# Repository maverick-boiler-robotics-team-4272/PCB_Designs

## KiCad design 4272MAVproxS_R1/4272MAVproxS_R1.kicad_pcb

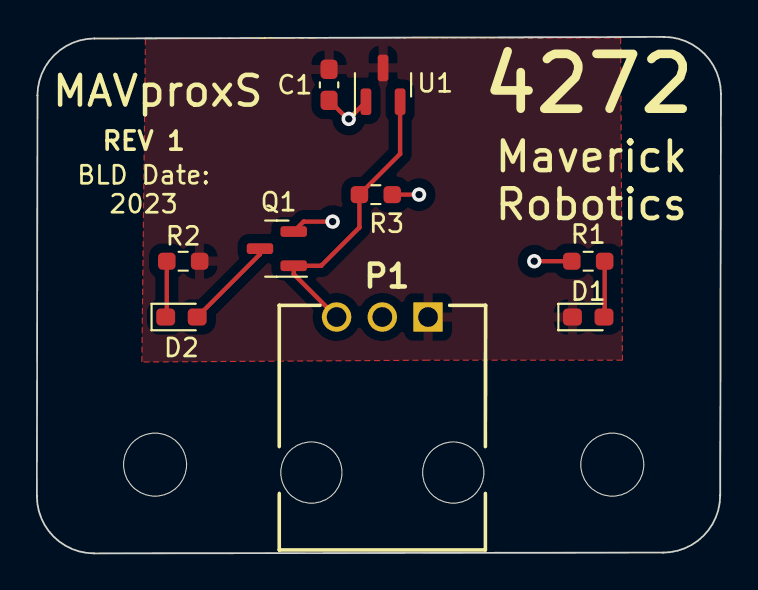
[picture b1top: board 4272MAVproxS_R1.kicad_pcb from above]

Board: 2 copper layers, 38.0 x 28.7 mm, 9 parts (0 on the bottom side), 6 nets.

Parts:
C1: 100nF; C_0603_1608Metric_Pad1.08x0.95mm_HandSolder
D1: RED; LED_0603_1608Metric_Pad1.05x0.95mm_HandSolder
D2: GRN; LED_0603_1608Metric_Pad1.05x0.95mm_HandSolder
P1: 15-91-7030; 705550037
Q1: FDN338P; SOT-23
R1, R2: 137; R_0603_1608Metric_Pad0.98x0.95mm_HandSolder
R3: 100K; R_0603_1608Metric_Pad0.98x0.95mm_HandSolder
U1: DRV5032FCBZR; SOT-23

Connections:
+3.3V: C1.1, P1.2, Q1.2 (S), R1.1, R3.2, U1.1 (VCC)
GND: C1.2, D1.1 (K), P1.1, R2.2, U1.3 (GND)
unnamed: D1.2 (A), R1.2
unnamed: D2.2 (A), Q1.3 (D)
unnamed: D2.1 (K), R2.1
unnamed: P1.3, Q1.1 (G), R3.1, U1.2 (OUT)

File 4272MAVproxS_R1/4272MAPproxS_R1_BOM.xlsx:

Line # | Ref Des | Quantity | Decription | Manufacturer | Part # | Footprint
1 | C1 | 1 | CAP CER 10000PF 50V C0G/NP0 | Murata | GRM1885C1H103JA01J | 0603
2 | D1 | 1 | LED T-1 Through hole red | Lite-On | LTL-4211N | T1
3 | D2 | 1 | LED T-1 Through hole green | Lite-On | LTL-45231 | T1
4 | P1 | 1 | SL Conn Header R/A 3Pos 2.54MM | Molex | 705550037 | SL RA 3
5 | Q1 | 1 | MOSFET P-CH 20V 1.6A | onsemi | FDN338P | SOT-23
6 | R1,R2 | 2 | RES 137 OHM 1% 1/10W | YAGEO | RC0603FR-07137RL | 0603
7 | R3 | 1 | RES 100k OHM 1% 1/10W | YAGEO | RC0603FR-07100KL | 0603
8 | U1 | 1 | Hall Effect Sensor Omnipolar | Texas Instruments | DRV5032FCLPGM | TO-92

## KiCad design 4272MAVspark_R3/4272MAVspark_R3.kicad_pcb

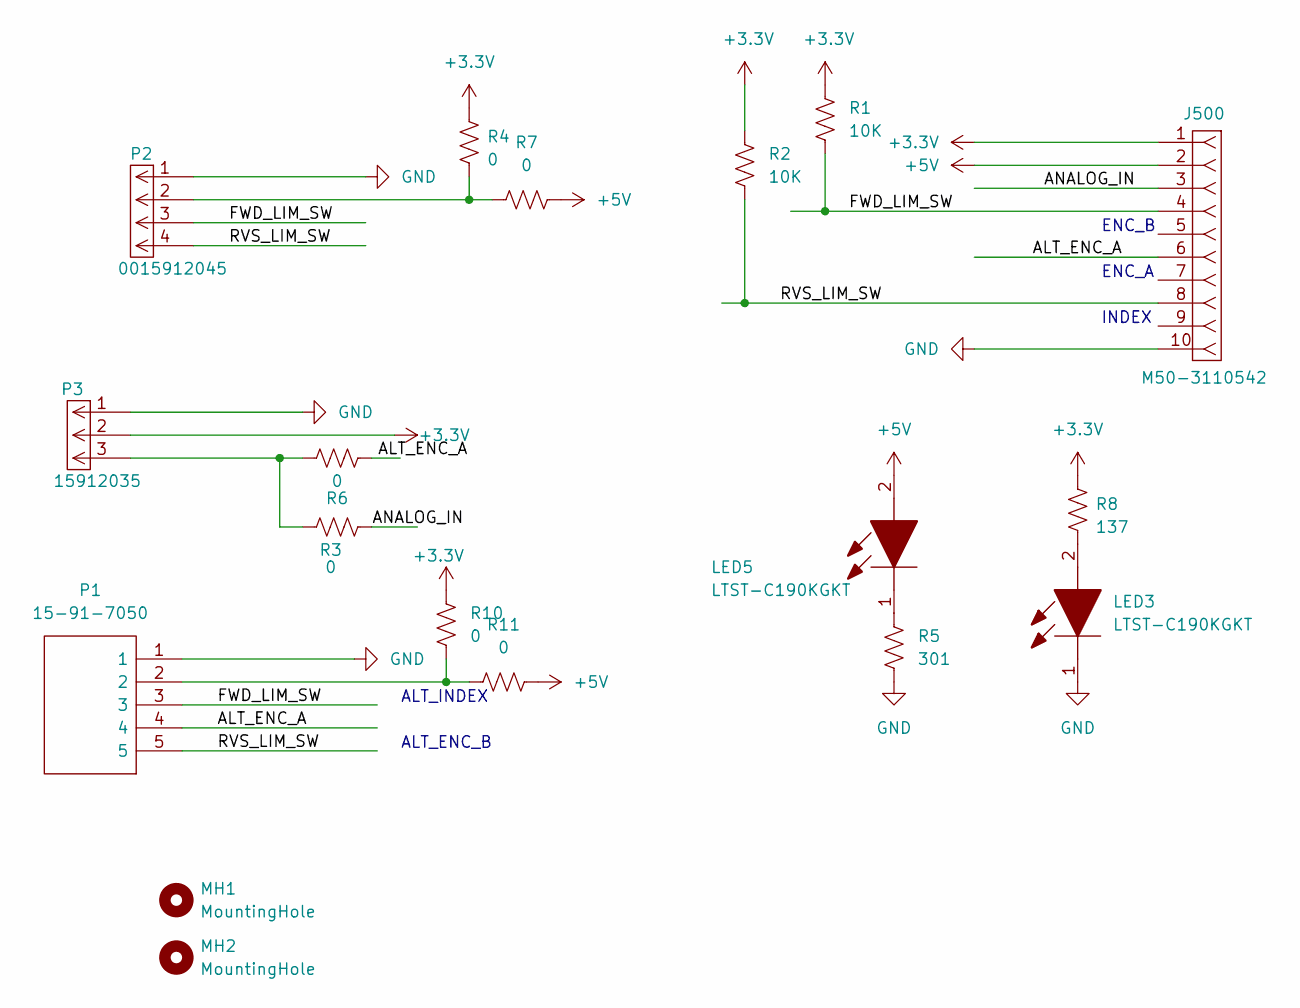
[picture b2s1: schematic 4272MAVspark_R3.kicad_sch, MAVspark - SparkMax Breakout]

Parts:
J500: M50-3110542; M503110542; Mouser Part Number 855-M50-3110542
LED3, LED5: LTST-C190KGKT; LED_0603_1608Metric_Pad1.05x0.95mm_HandSolder; Mouser Part Number 859-LTST-C190KGKT
MH1, MH2: MountingHole; MountingHole_3.2mm_M3
P1: 15-91-7050; 15917050; Manufacturer_Part_Number 15-91-7050; Mouser Part Number 538-15-91-7050
P2: 0015912045; Manufacturer_Part_Number 0015912045; Mouser Part Number N/A
P3: 15912035; Mouser Part Number 538-15-91-7030
R1, R2: 10K; R_0603_1608Metric_Pad0.98x0.95mm_HandSolder
R3, R4, R6, R7, R10, R11: 0; R_0805_2012Metric_Pad1.20x1.40mm_HandSolder
R5: 301; R_0603_1608Metric_Pad0.98x0.95mm_HandSolder
R8: 137; R_0603_1608Metric_Pad0.98x0.95mm_HandSolder

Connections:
+3.3V: J500.1, P3.2, R1.2, R2.1, R4.2, R8.1, R10.1
+5V: J500.2, LED5.2, R7.1, R11.1
/ALT_ENC_A: J500.6, P1.4, R6.2
/ANALOG_IN: J500.3, R3.2
/FWD_LIM_SW: J500.4, P1.3, P2.3, R1.1
/RVS_LIM_SW: J500.8, P1.5, P2.4, R2.2
GND: J500.10, LED3.1, P1.1, P2.1, P3.1, R5.2
unnamed: LED3.2, R8.2
unnamed: LED5.1, R5.1
unnamed: P1.2, R10.2, R11.2
unnamed: P2.2, R4.1, R7.2
unnamed: P3.3, R3.1, R6.1

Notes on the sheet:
ALT_ENC_B
ALT_INDEX
ENC_B
INDEX
ENC_A

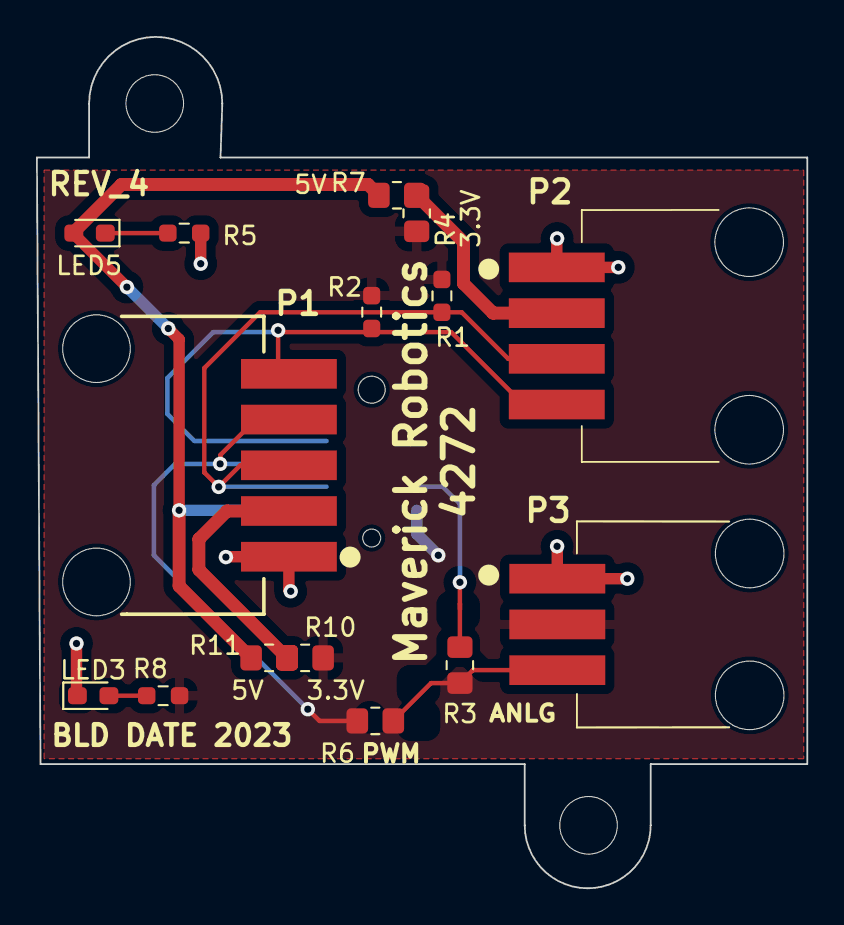
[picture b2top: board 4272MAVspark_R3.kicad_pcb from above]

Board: 2 copper layers, 42.8 x 47.3 mm, 17 parts (1 on the bottom side), 12 nets.

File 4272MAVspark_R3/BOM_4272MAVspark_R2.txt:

REFDES	QTY	DIGI-KEY #		MANUF		PART #			DESCRIPTION
LED3	1	160-1435-1-ND		Lite-On Inc.	LTST-C190KGKT		LED GREEN 0603 SMD
LED5	1	160-1435-1-ND		Lite-On Inc.	LTST-C190KGKT		LED GREEN 0603 SMD
R1, R2	2									RES 10K
R3	1	311-137HRCT-ND		YAGEO		RC0603FR-07137RL	RES 137 0603 1%	
R5	1									RES 301 0603 1%
R6	0									RES 0 0805
R7	1									RES 0 0805
R10	0									RES 0 0805
R11	0									RES 0 0805
P1	0
P2	1
P3	1
J500	1

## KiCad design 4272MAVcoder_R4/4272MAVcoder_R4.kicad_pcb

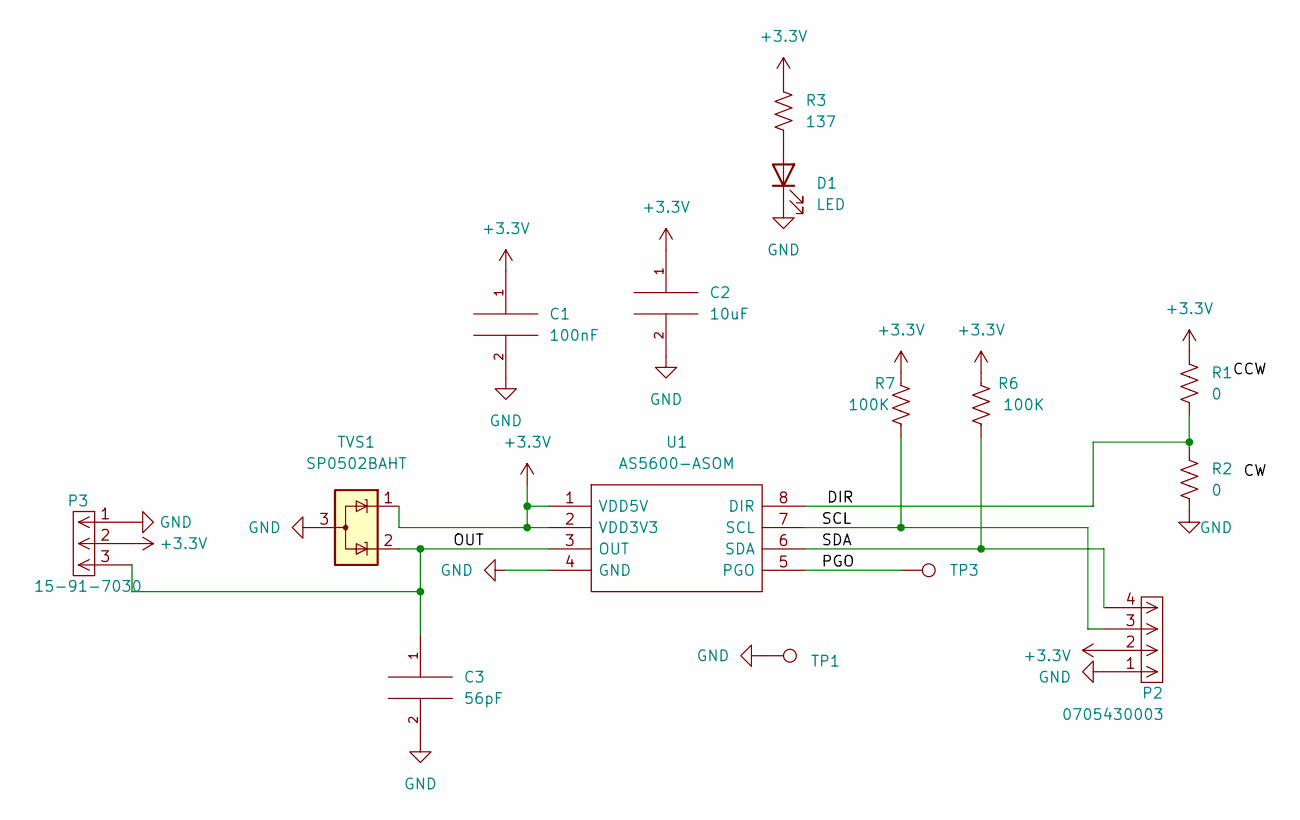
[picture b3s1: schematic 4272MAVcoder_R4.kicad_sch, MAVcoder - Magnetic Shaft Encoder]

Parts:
C1: 100nF; C_0603_1608Metric_Pad1.08x0.95mm_HandSolder
C2: 10uF; C_0805_2012Metric_Pad1.18x1.45mm_HandSolder
C3: 56pF; C_0603_1608Metric_Pad1.08x0.95mm_HandSolder
D1: LED; LED_D3.0mm
P2: 0705430003; Molex_SL_171971-0004_1x04_P2.54mm_Vertical; Manufacturer_Part_Number 0015912045; Mouser Part Number N/A
P3: 15-91-7030; 705550037; Mouser Part Number 538-15-91-7030
R1, R2: 0; R_0603_1608Metric_Pad0.98x0.95mm_HandSolder
R3: 137; R_0603_1608Metric_Pad0.98x0.95mm_HandSolder
R6, R7: 100K; R_0603_1608Metric_Pad0.98x0.95mm_HandSolder
TP1, TP3: TestPoint; TestPoint_THTPad_1.0x1.0mm_Drill0.5mm
TVS1: SP0502BAHT; SOT-23
U1: AS5600-ASOM; SOIC-8_3.9x4.9mm_P1.27mm; Mouser Part Number 985-AS5600-ASOM

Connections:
+3.3V: C1.1, C2.1, P2.2, R1.1, R3.1, R6.2, R7.2, TVS1.1 (K), U1.1 (VDD5V), U1.2 (VDD3V3); also elsewhere on the board
/DIR: R1.2, R2.1, U1.8 (DIR)
/OUT: C3.1, TVS1.2 (K), U1.3 (OUT); also elsewhere on the board
/PGO: TP3.1, U1.5 (PGO)
/SCL: P2.3, R7.1, U1.7 (SCL)
/SDA: P2.4, R6.1, U1.6 (SDA)
GND: C1.2, C2.2, C3.2, D1.1 (K), P2.1, R2.2, TP1.1, TVS1.3 (A), U1.4 (GND); also elsewhere on the board
unnamed: D1.2 (A), R3.2

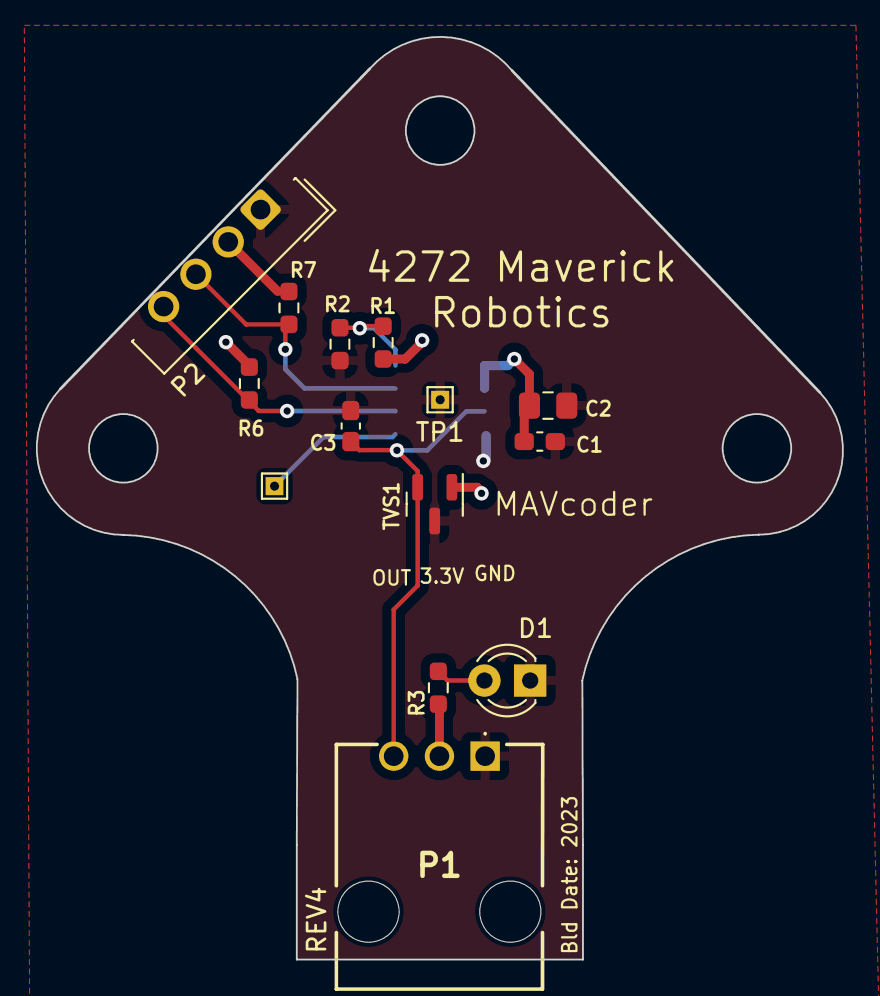
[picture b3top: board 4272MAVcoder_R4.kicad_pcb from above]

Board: 2 copper layers, 44.8 x 51.3 mm, 15 parts (1 on the bottom side), 8 nets.

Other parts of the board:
P1: 15-91-7030; 705550037

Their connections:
+3.3V: P1.2; also elsewhere on the board
/OUT: P1.3; also elsewhere on the board
GND: P1.1; also elsewhere on the board

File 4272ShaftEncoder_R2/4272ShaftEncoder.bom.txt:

REFDES	QTY	DIGI-KEY #		MANUF		PART #			DESCRIPTION
C1	1	587-1245-1-ND 		Taiyo Yuden	TMK107BJ104KA-T		CAP 0.1uF 0603 10% SMD
C2	1	587-1300-1-ND		Taiyo Yuden	LMK212BJ106KG-T		CAP 10uF 0805 10% SMD
C3	1	311-1066-1-ND		YAGEO		CC0603JRNPO9BN560	CAP 56pF 0603 SMD
LED3	1	160-1435-1-ND		Lite-On Inc.	LTST-C190KGKT		LED GREEN 0603 SMD
R1	1	311-0.0HRCT-ND		YAGEO		RC0603FR-070RL		RES 0 0603
R3	1	311-137HRCT-ND		YAGEO		RC0603FR-07137RL	RES 137 0603 1%	
R6,R7	2	311-100KLDCT-ND		YAGEO		AC0603FR-07100KL	RES 100K 0603 1%
TVS1 	1	F2714CT-ND		Littelfuse Inc.	SP0502BAHTG		TVS 8.5V CLAMP	
U1	1	AS5600-ASOMCT-ND	ams		AS5600-ASOM		Hall Effect Angle Sensor

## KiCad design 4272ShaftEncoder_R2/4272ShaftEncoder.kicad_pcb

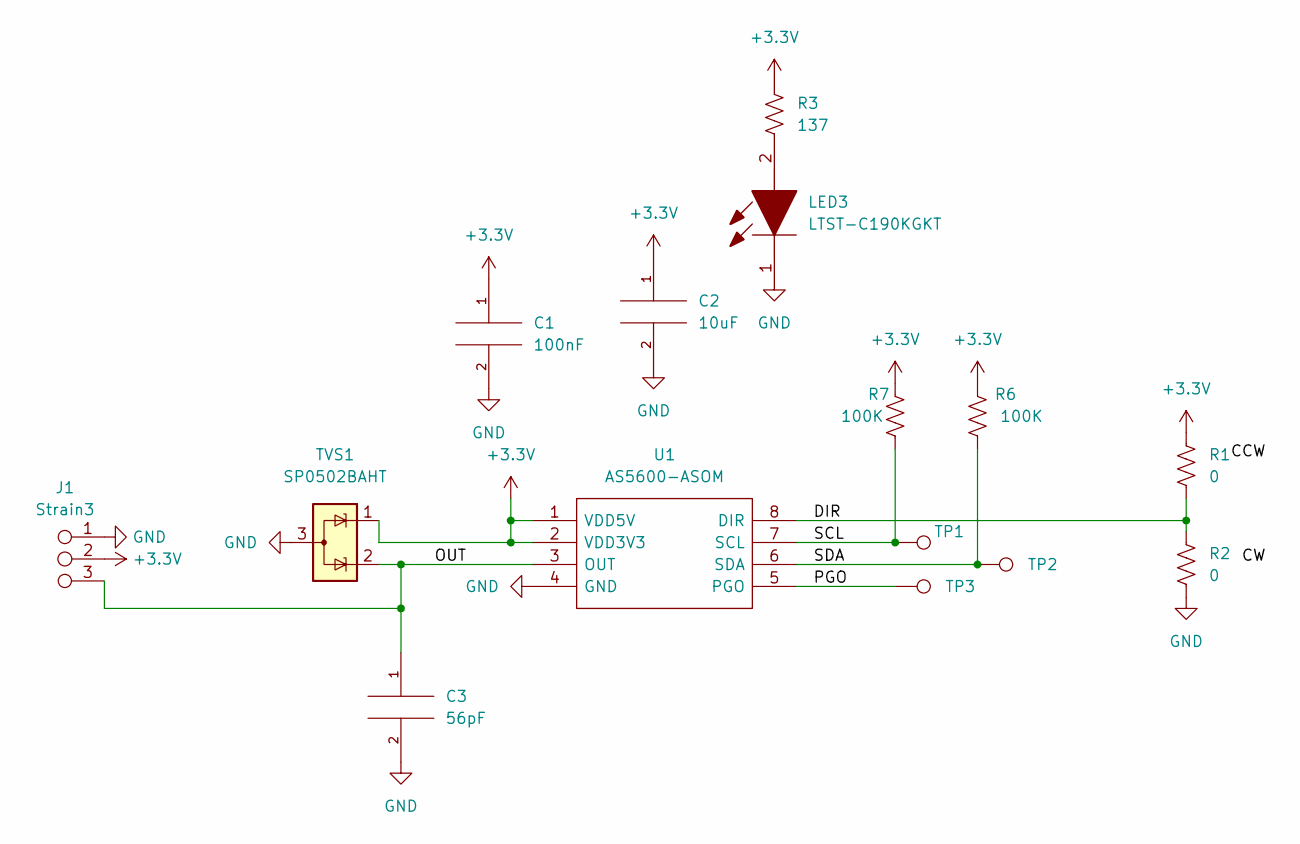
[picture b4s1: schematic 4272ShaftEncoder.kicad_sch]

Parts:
C1: 100nF; C_0603_1608Metric_Pad1.08x0.95mm_HandSolder
C2: 10uF; C_0805_2012Metric_Pad1.18x1.45mm_HandSolder
C3: 56pF; C_0603_1608Metric_Pad1.08x0.95mm_HandSolder
J1: Strain3; 3Pin Strain Relief 1x03 2.54mm
LED3: LTST-C190KGKT; LED_0603_1608Metric_Pad1.05x0.95mm_HandSolder; Mouser Part Number 859-LTST-C190KGKT
R1, R2: 0; R_0603_1608Metric_Pad0.98x0.95mm_HandSolder
R3: 137; R_0603_1608Metric_Pad0.98x0.95mm_HandSolder
R6, R7: 100K; R_0603_1608Metric_Pad0.98x0.95mm_HandSolder
TP1, TP2, TP3: TestPoint; TestPoint_THTPad_1.0x1.0mm_Drill0.5mm
TVS1: SP0502BAHT; SOT-23
U1: AS5600-ASOM; SOIC-8_3.9x4.9mm_P1.27mm; Mouser Part Number 985-AS5600-ASOM

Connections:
+3.3V: C1.1, C2.1, J1.2, R1.1, R3.1, R6.2, R7.2, TVS1.1 (K), U1.1 (VDD5V), U1.2 (VDD3V3)
/DIR: R1.2, R2.1, U1.8 (DIR)
/OUT: C3.1, J1.3, TVS1.2 (K), U1.3 (OUT)
/PGO: TP3.1, U1.5 (PGO)
/SCL: R7.1, TP1.1, U1.7 (SCL)
/SDA: R6.1, TP2.1, U1.6 (SDA)
GND: C1.2, C2.2, C3.2, J1.1, LED3.1, R2.2, TVS1.3 (A), U1.4 (GND)
unnamed: LED3.2, R3.2

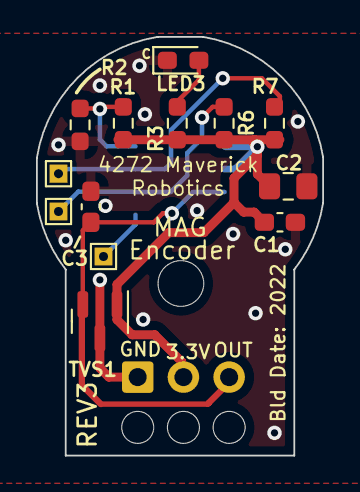
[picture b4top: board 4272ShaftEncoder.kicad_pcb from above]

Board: 2 copper layers, 15.9 x 23.3 mm, 15 parts (1 on the bottom side), 8 nets.

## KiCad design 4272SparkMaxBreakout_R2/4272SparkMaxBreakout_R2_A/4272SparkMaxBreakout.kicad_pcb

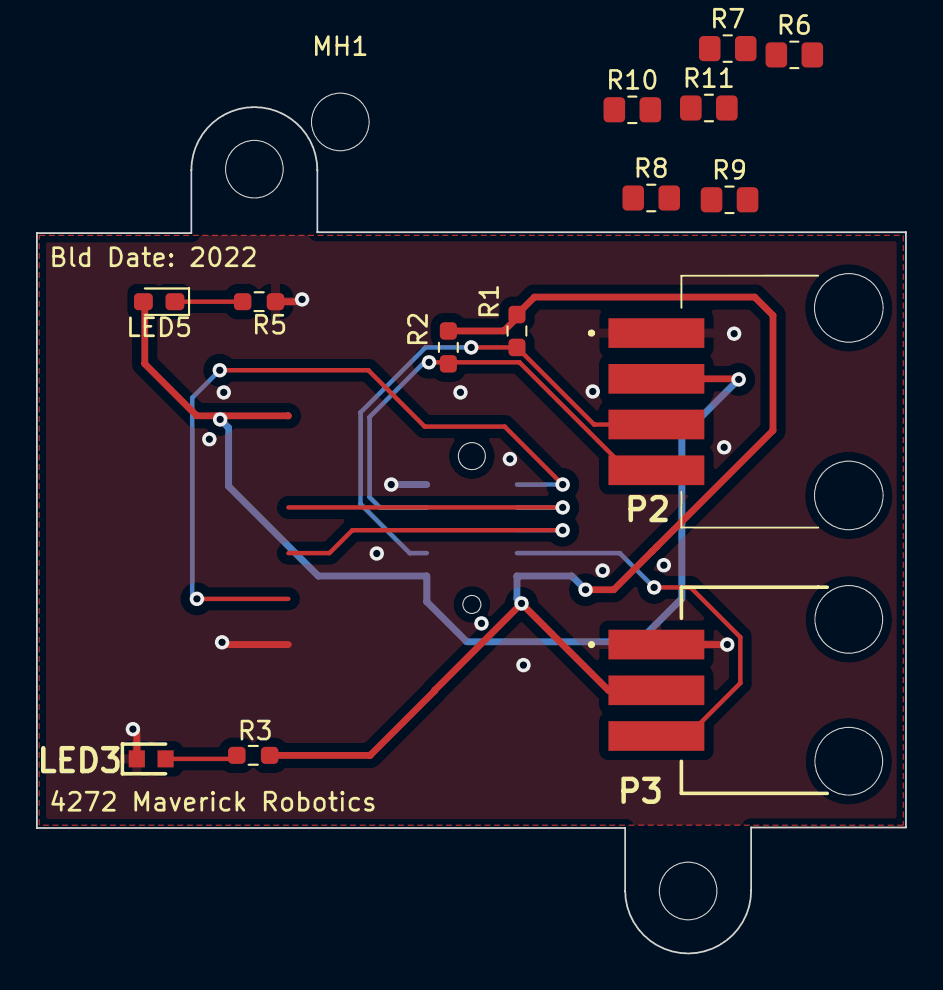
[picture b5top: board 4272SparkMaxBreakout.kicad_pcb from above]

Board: 2 copper layers, 48.3 x 47.0 mm, 17 parts (1 on the bottom side), 10 nets.

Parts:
J500: M50-3110542; M503110542_MOD
LED3: LTST-C190KGKT; LEDC1608X80N
LED5: LTST-C190KGKT; LED_0603_1608Metric_Pad1.05x0.95mm_HandSolder
MH1, MH2: MountingHole; MountingHole_3.2mm_M3
P2: 0015912045
P3: 15-91-7030; 15917030
R1, R2: 10K; R_0603_1608Metric_Pad0.98x0.95mm_HandSolder
R3: 137; R_0603_1608Metric_Pad0.98x0.95mm_HandSolder
R5: 301; R_0603_1608Metric_Pad0.98x0.95mm_HandSolder
R6, R7, R8, R9, R10, R11: 0; R_0805_2012Metric_Pad1.20x1.40mm_HandSolder

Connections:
+3.3V: J500.1, P3.2, R1.2, R2.1, R3.1, R6.2, R8.1, R10.1
+5V: J500.2, LED5.2, P2.2, R7.1, R9.1, R11.1
/ANALOG_IN: J500.3, P3.3
/FWD_LIM_SW: J500.4, P2.3, R1.1
/RVS_LIM_SW: J500.8, P2.4, R2.2
GND: J500.10, LED3.1, P2.1, P3.1, R5.2
unnamed: LED5.1, R5.1
unnamed: R10.2, R11.2
unnamed: R6.1, R7.2
unnamed: R8.2, R9.2

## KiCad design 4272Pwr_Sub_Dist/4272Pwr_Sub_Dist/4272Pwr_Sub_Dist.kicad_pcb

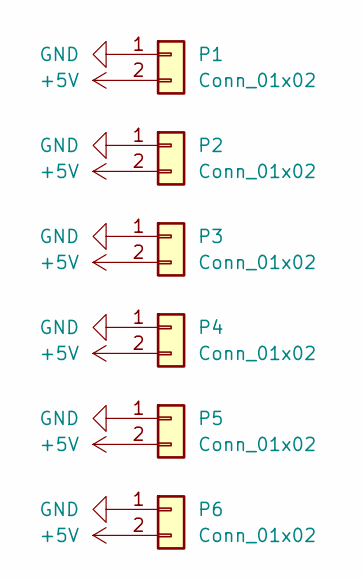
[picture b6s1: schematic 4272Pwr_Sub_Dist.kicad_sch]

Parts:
P1, P2, P3, P4, P5, P6: Conn_01x02; Molex_SL_171971-0002_1x02_P2.54mm_Vertical

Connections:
+5V: P1.2, P2.2, P3.2, P4.2, P5.2, P6.2
GND: P1.1, P2.1, P3.1, P4.1, P5.1, P6.1

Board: 2 copper layers, 6 parts (0 on the bottom side), 2 nets, no tracks yet.

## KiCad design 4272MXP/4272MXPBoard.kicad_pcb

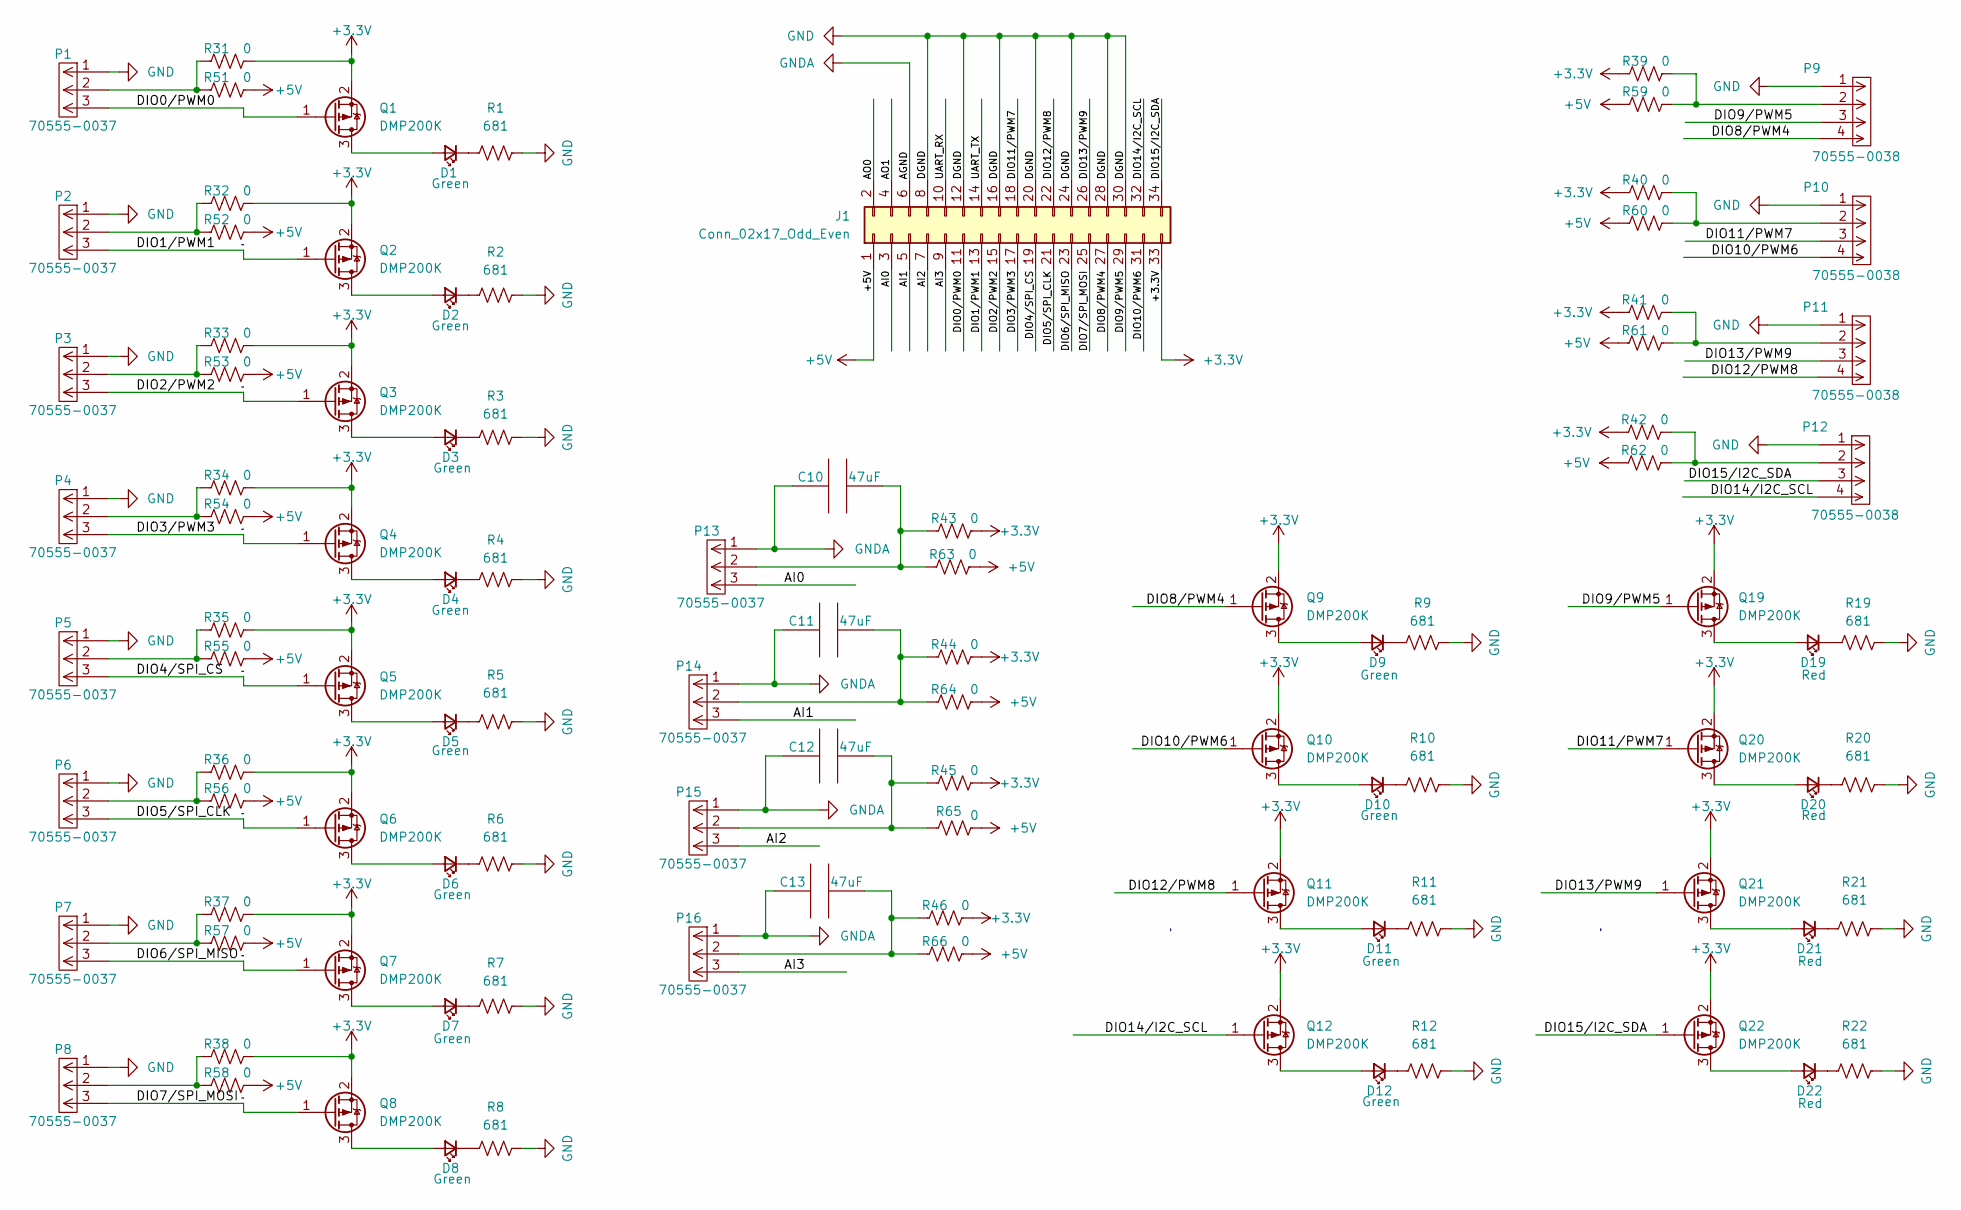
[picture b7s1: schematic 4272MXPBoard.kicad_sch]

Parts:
C10, C11, C12, C13: 47uF; C_0805_2012Metric_Pad1.18x1.45mm_HandSolder; Part # C2012X5R1A476M125AC
D1, D2, D3, D4, D5, D6, D7, D8, D9, D10, D11, D12: Green; LED_D3.0mm
D19, D20, D21, D22: Red; LED_D3.0mm
J1: Conn_02x17_Odd_Even; PinSocket_2x17_P2.54mm_Vertical
P1, P2, P3, P4, P5, P6, P7, P8, P13, P14, P15, P16: 70555-0037; 705550037; Mouser Part Number 538-15-91-7030
P9, P10, P11, P12: 70555-0038; 705550038; Mouser Part Number 538-15-91-7030
Q1, Q2, Q3, Q4, Q5, Q6, Q7, Q8, Q9, Q10, Q11, Q12, Q19, Q20, Q21, Q22: DMP200K; SOT-23
R1, R2, R3, R4, R5, R6, R7, R8, R9, R10, R11, R12, R19, R20, R21, R22: 681; R_0603_1608Metric_Pad0.98x0.95mm_HandSolder
R31, R32, R33, R34, R35, R36, R37, R38, R39, R40, R41, R42, R43, R44, R45, R46, R51, R52, R53, R54, R55, R56, R57, R58, R59, R60, R61, R62, R63, R64, R65, R66: 0; R_0805_2012Metric_Pad1.20x1.40mm_HandSolder

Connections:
+3.3V: J1.33, Q1.2 (S), Q2.2 (S), Q3.2 (S), Q4.2 (S), Q5.2 (S), Q6.2 (S), Q7.2 (S), Q8.2 (S), Q9.2 (S), Q10.2 (S), Q11.2 (S), Q12.2 (S), Q19.2 (S), Q20.2 (S), Q21.2 (S), Q22.2 (S), R31.2, R32.2, R33.2, R34.2, R35.2, R36.2, R37.2, R38.2, R39.1, R40.1, R41.1, R42.1, R43.2, R44.2, R45.2, R46.2
+5V: J1.1, R51.2, R52.2, R53.2, R54.2, R55.2, R56.2, R57.2, R58.2, R59.1, R60.1, R61.1, R62.1, R63.2, R64.2, R65.2, R66.2
/AI0: J1.3, P13.3
/AI1: J1.5, P14.3
/AI2: J1.7, P15.3
/AI3: J1.9, P16.3
/AO0: J1.2
/AO1: J1.4
/DIO0/PWM0: J1.11, P1.3, Q1.1 (G)
/DIO1/PWM1: J1.13, P2.3, Q2.1 (G)
/DIO2/PWM2: J1.15, P3.3, Q3.1 (G)
/DIO3/PWM3: J1.17, P4.3, Q4.1 (G)
/DIO4/SPI_CS: J1.19, P5.3, Q5.1 (G)
/DIO5/SPI_CLK: J1.21, P6.3, Q6.1 (G)
/DIO6/SPI_MISO: J1.23, P7.3, Q7.1 (G)
/DIO7/SPI_MOSI: J1.25, P8.3, Q8.1 (G)
/DIO8/PWM4: J1.27, P9.4, Q9.1 (G)
/DIO9/PWM5: J1.29, P9.3, Q19.1 (G)
/DIO10/PWM6: J1.31, P10.4, Q10.1 (G)
/DIO11/PWM7: J1.18, P10.3, Q20.1 (G)
/DIO12/PWM8: J1.22, P11.4, Q11.1 (G)
/DIO13/PWM9: J1.26, P11.3, Q21.1 (G)
/DIO14/I2C_SCL: J1.32, P12.4, Q12.1 (G)
/DIO15/I2C_SDA: J1.34, P12.3, Q22.1 (G)
/UART_RX: J1.10
/UART_TX: J1.14
GND: J1.8, J1.12, J1.16, J1.20, J1.24, J1.28, J1.30, P1.1, P2.1, P3.1, P4.1, P5.1, P6.1, P7.1, P8.1, P9.1, P10.1, P11.1, P12.1, R1.2, R2.2, R3.2, R4.2, R5.2, R6.2, R7.2, R8.2, R9.2, R10.2, R11.2, R12.2, R19.2, R20.2, R21.2, R22.2
GNDA: C10.1, C11.1, C12.1, C13.1, J1.6, P13.1, P14.1, P15.1, P16.1
unnamed: D1.1 (K), R1.1
unnamed: D1.2 (A), Q1.3 (D)
unnamed: D2.1 (K), R2.1
unnamed: D2.2 (A), Q2.3 (D)
unnamed: D3.1 (K), R3.1
unnamed: D3.2 (A), Q3.3 (D)
unnamed: D4.1 (K), R4.1
unnamed: D4.2 (A), Q4.3 (D)
unnamed: D5.1 (K), R5.1
unnamed: D5.2 (A), Q5.3 (D)
unnamed: D6.1 (K), R6.1
unnamed: D6.2 (A), Q6.3 (D)
unnamed: D7.1 (K), R7.1
unnamed: D7.2 (A), Q7.3 (D)
unnamed: D8.1 (K), R8.1
unnamed: D8.2 (A), Q8.3 (D)
unnamed: D9.1 (K), R9.1
unnamed: D9.2 (A), Q9.3 (D)
unnamed: D10.1 (K), R10.1
unnamed: D10.2 (A), Q10.3 (D)
unnamed: D11.1 (K), R11.1
unnamed: D11.2 (A), Q11.3 (D)
unnamed: D12.1 (K), R12.1
unnamed: D12.2 (A), Q12.3 (D)
unnamed: D19.1 (K), R19.1
unnamed: D19.2 (A), Q19.3 (D)
unnamed: D20.1 (K), R20.1
unnamed: D20.2 (A), Q20.3 (D)
unnamed: D21.1 (K), R21.1
unnamed: D21.2 (A), Q21.3 (D)
unnamed: D22.1 (K), R22.1
unnamed: D22.2 (A), Q22.3 (D)
unnamed: P1.2, R31.1, R51.1
unnamed: P2.2, R32.1, R52.1
unnamed: P3.2, R33.1, R53.1
unnamed: P4.2, R34.1, R54.1
unnamed: P5.2, R35.1, R55.1
unnamed: P6.2, R36.1, R56.1
unnamed: P7.2, R37.1, R57.1
unnamed: P8.2, R38.1, R58.1
unnamed: P9.2, R39.2, R59.2
unnamed: P10.2, R40.2, R60.2
unnamed: P11.2, R41.2, R61.2
unnamed: P12.2, R42.2, R62.2
unnamed: C10.2, P13.2, R43.1, R63.1
unnamed: C11.2, P14.2, R44.1, R64.1
unnamed: C12.2, P15.2, R45.1, R65.1
unnamed: C13.2, P16.2, R46.1, R66.1

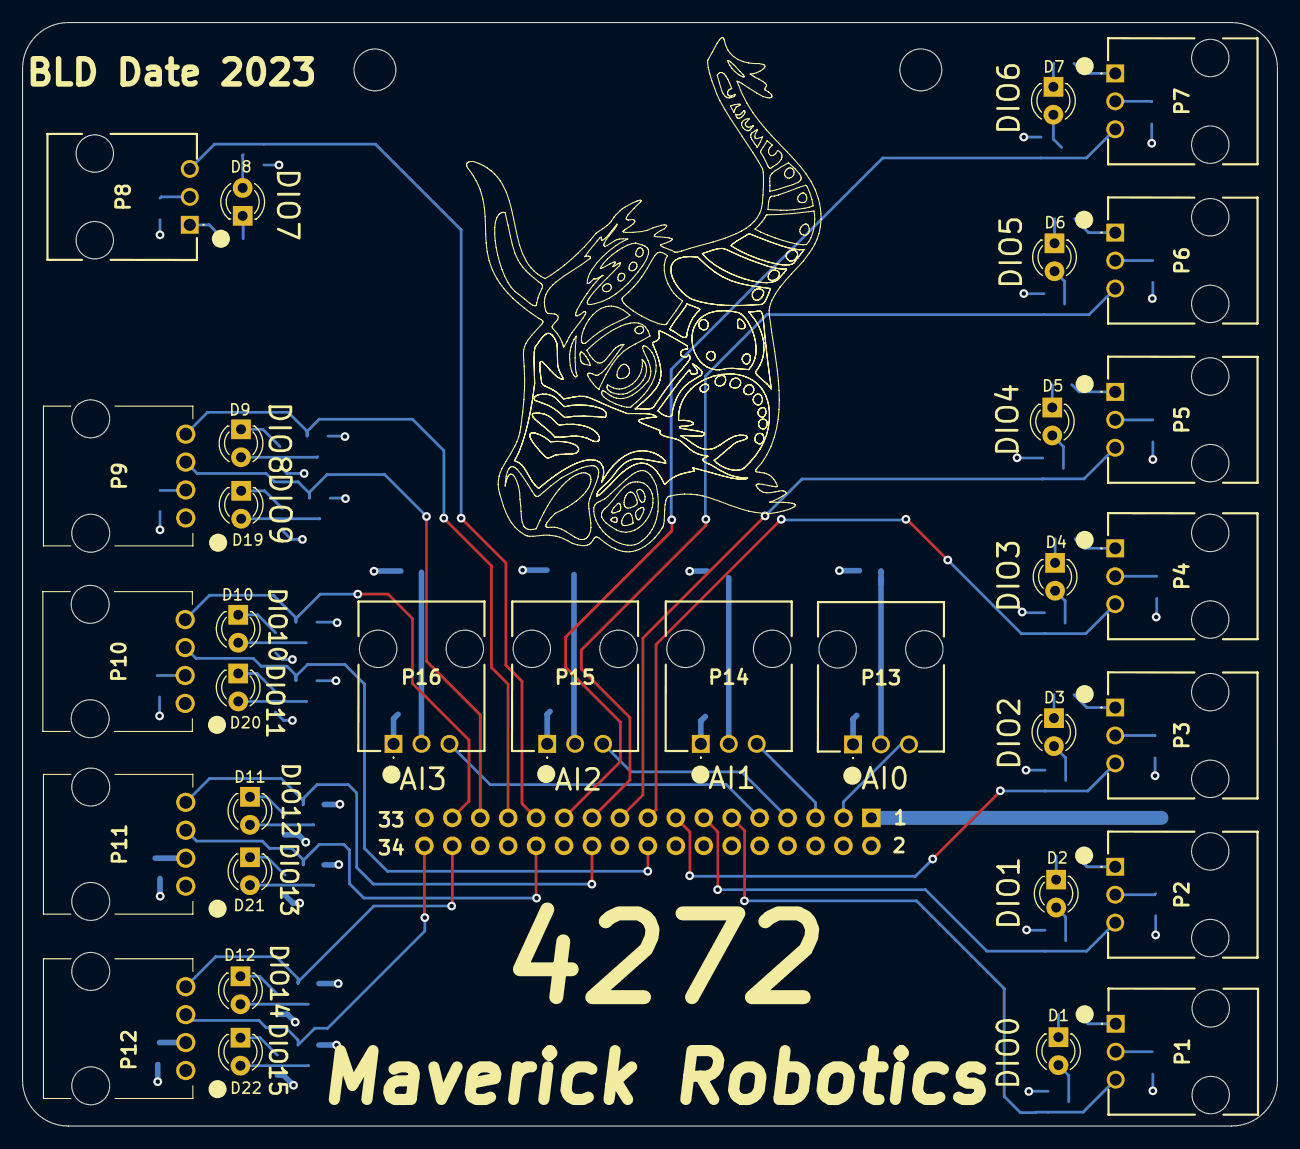
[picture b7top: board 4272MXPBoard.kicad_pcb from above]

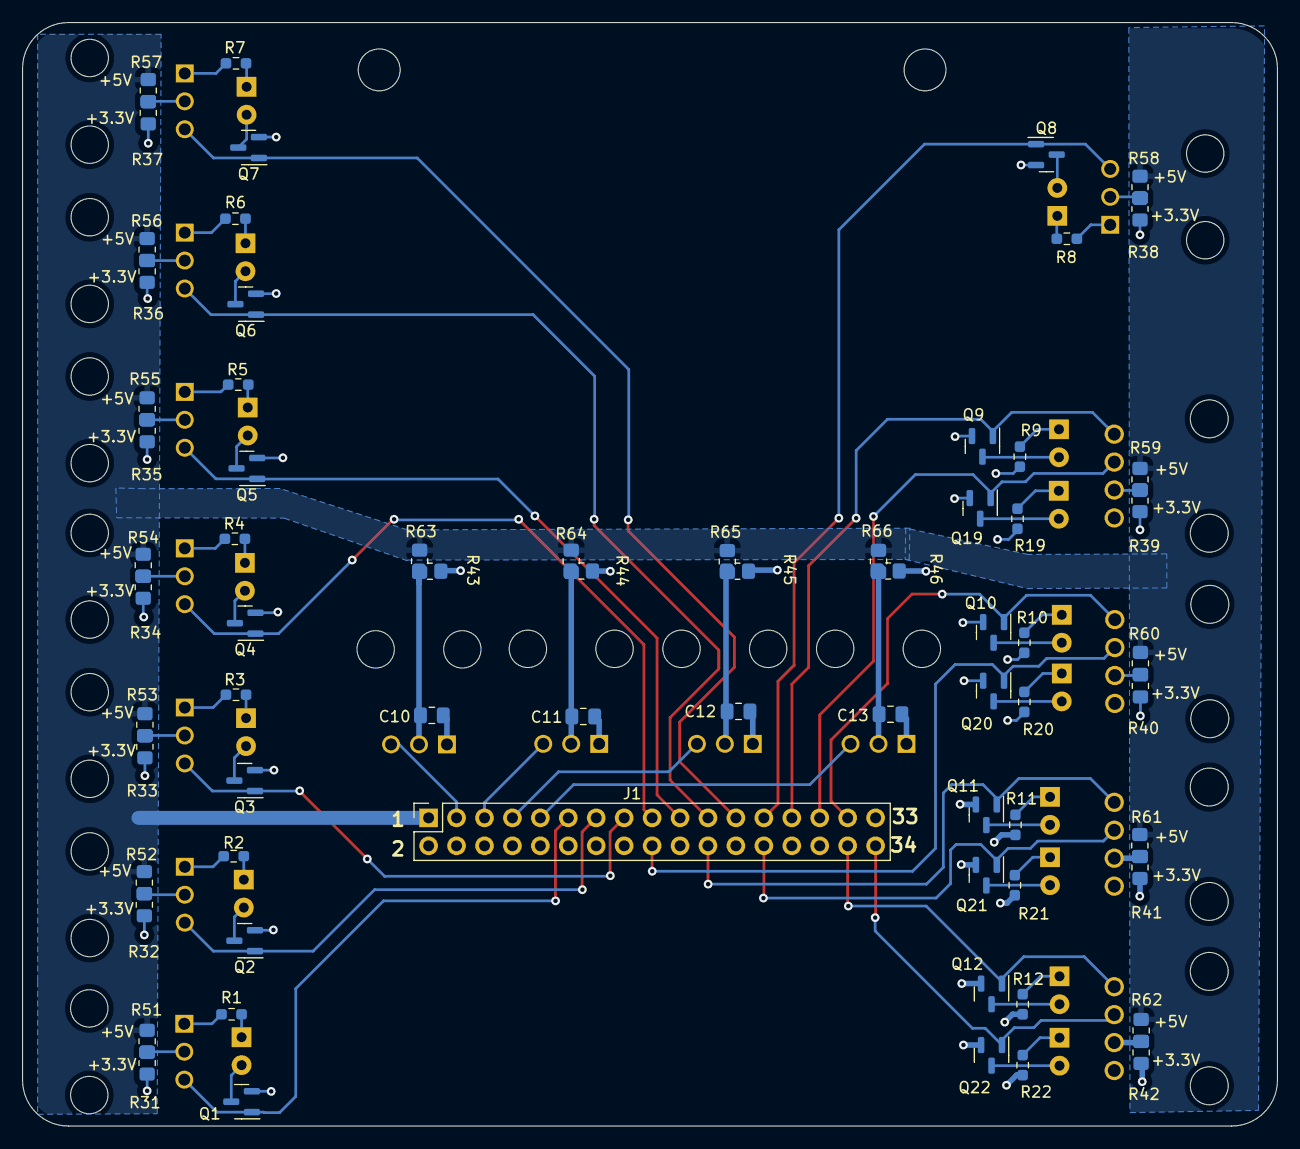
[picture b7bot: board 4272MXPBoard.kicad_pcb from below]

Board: 4 copper layers, 114.1 x 100.3 mm, 101 parts (69 on the bottom side), 72 nets.

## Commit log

2022-10-27 first commmit
2022-11-01 Remove incorrect files
2022-12-07 Add new files
2022-12-09 Add pre-season archive
2023-11-07 Add Rev 4 MAVcoder -- Magnetic Shaft Encoder
2023-11-10 Add MAVprox REV 1 Hall Effect Sensor
2023-12-28 Add preseason PCB designs
